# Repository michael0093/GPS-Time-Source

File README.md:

# GPS-Time-Source
GPS Time Source based on Quectel LC29T EVB

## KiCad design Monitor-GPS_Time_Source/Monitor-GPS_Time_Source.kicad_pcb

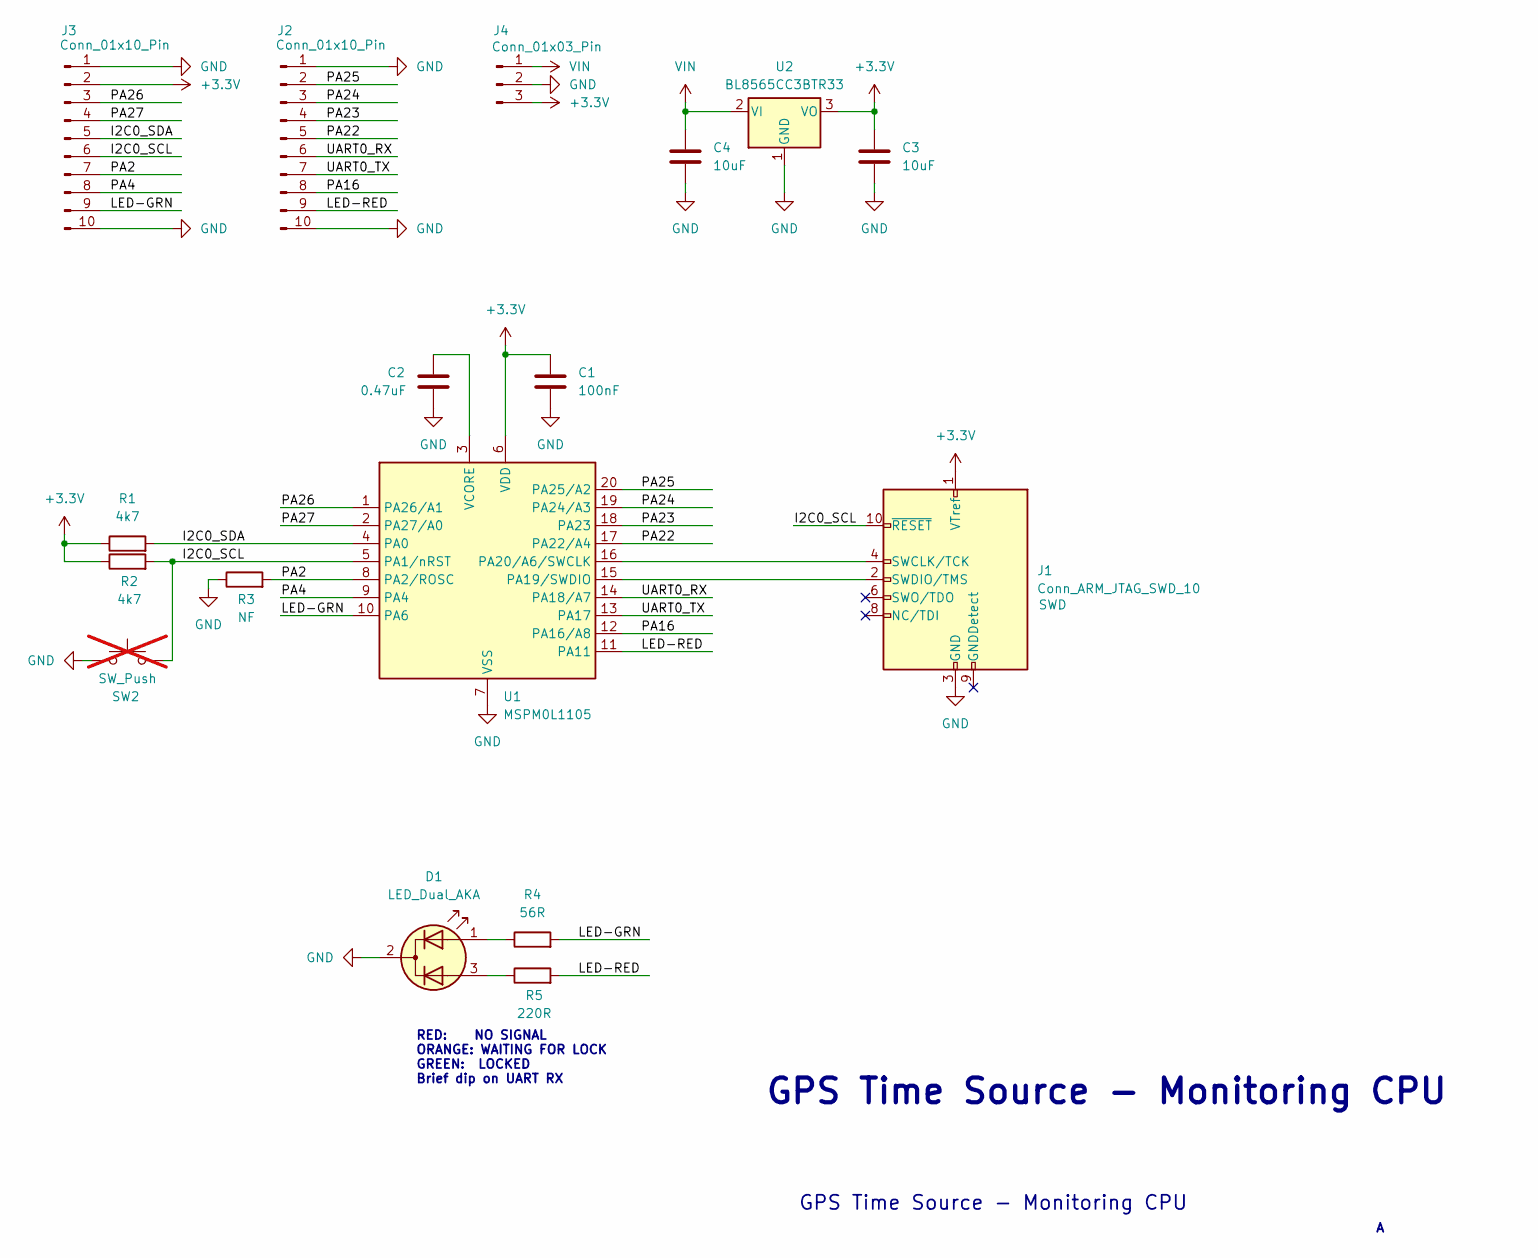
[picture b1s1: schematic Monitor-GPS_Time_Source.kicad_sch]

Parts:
C1: 100nF; C_0603_1608Metric
C2: 0.47uF; C_0603_1608Metric
C3, C4: 10uF; C_0805_2012Metric
D1: LED_Dual_AKA; LED_D3.0mm-3
J1: Conn_ARM_JTAG_SWD_10; PinHeader_2x05_P1.27mm_Vertical_SMD
J2, J3: Conn_01x10_Pin; PinHeader_1x10_P2.54mm_Vertical
J4: Conn_01x03_Pin; PinHeader_1x03_P2.54mm_Vertical
R1, R2: 4k7; R_0603_1608Metric
R3: NF; R_0603_1608Metric
R4: 56R; R_0603_1608Metric
R5: 220R; R_0603_1608Metric
SW2: SW_Push; SW_Push_SPST_NO_Alps_SKRK; not fitted
U1: MSPM0L1105; TSSOP-20_4.4x5mm_P0.5mm
U2: BL8565CC3BTR33; SOT-89-3

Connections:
+3.3V: C1.1, C3.1, J1.1 (VTref), J3.2, J4.3, R1.1, R2.1, U1.6 (VDD), U2.3 (VO)
/I2C0_SCL: J1.10 (~RESET), J3.6, R2.2, SW2.2, U1.5 (PA1/nRST)
/I2C0_SDA: J3.5, R1.2, U1.4 (PA0)
/LED-GRN: J3.9, R4.2, U1.10 (PA6)
/LED-RED: J2.9, R5.2, U1.11 (PA11)
/PA2: J3.7, R3.2, U1.8 (PA1/ROSC)
/PA4: J3.8, U1.9 (PA4)
/PA16: J2.8, U1.12 (PA16/A8)
/PA22: J2.5, U1.17 (PA22/A4)
/PA23: J2.4, U1.18 (PA23)
/PA24: J2.3, U1.19 (PA24/A3)
/PA25: J2.2, U1.20 (PA25/A2)
/PA26: J3.3, U1.1 (PA26/A1)
/PA27: J3.4, U1.2 (PA27/A0)
/UART0_RX: J2.6, U1.14 (PA18/A7)
/UART0_TX: J2.7, U1.13 (PA17)
GND: C1.2, C2.2, C3.2, C4.2, D1.2 (K), J1.3 (GND), J1.5 (GND), J2.1, J2.10, J3.1, J3.10, J4.2, R3.1, SW2.1, U1.7 (VSS), U2.1 (GND)
unnamed: D1.1 (A1), R4.1
unnamed: D1.3 (A2), R5.1
unnamed: J1.4 (SWCLK/TCK), U1.16 (PA20/A6/SWCLK)
unnamed: J1.2 (SWDIO/TMS), U1.15 (PA19/SWDIO)
unnamed: C2.1, U1.3 (VCORE)
VIN: C4.1, J4.1, U2.2 (VI)

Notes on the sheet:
GPS Time Source - Monitoring CPU
RED: NO SIGNAL ORANGE: WAITING FOR LOCK GREEN: LOCKED Brief dip on UART RX

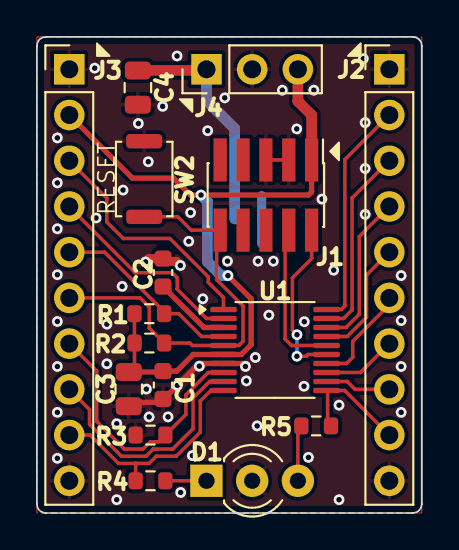
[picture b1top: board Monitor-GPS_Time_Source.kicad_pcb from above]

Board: 2 copper layers, 21.4 x 26.5 mm, 17 parts (1 on the bottom side), 23 nets.

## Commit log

2024-10-29 add firmware with basic functionality
2024-10-30 working on new state machines
2024-10-30 working on new state machine. Renamed project
2024-10-31 add state for two data bursts. Rearrange LED
2024-10-31 Release candidate FW for MSPM01306. Add first PCB files
2024-11-01 PCB work
2024-11-05 PCB layout complete, needs silkscreen work
2024-11-06 Add silkscreen text. Update sch to support MSPM0C110x
2024-11-07 Updated silkscreen for MSPM0. Finished DRC edits
2025-12-15 Update code to match PCB rev A (was EVB). Minor sch corrections
2025-12-27 Add case, label, and final photos
